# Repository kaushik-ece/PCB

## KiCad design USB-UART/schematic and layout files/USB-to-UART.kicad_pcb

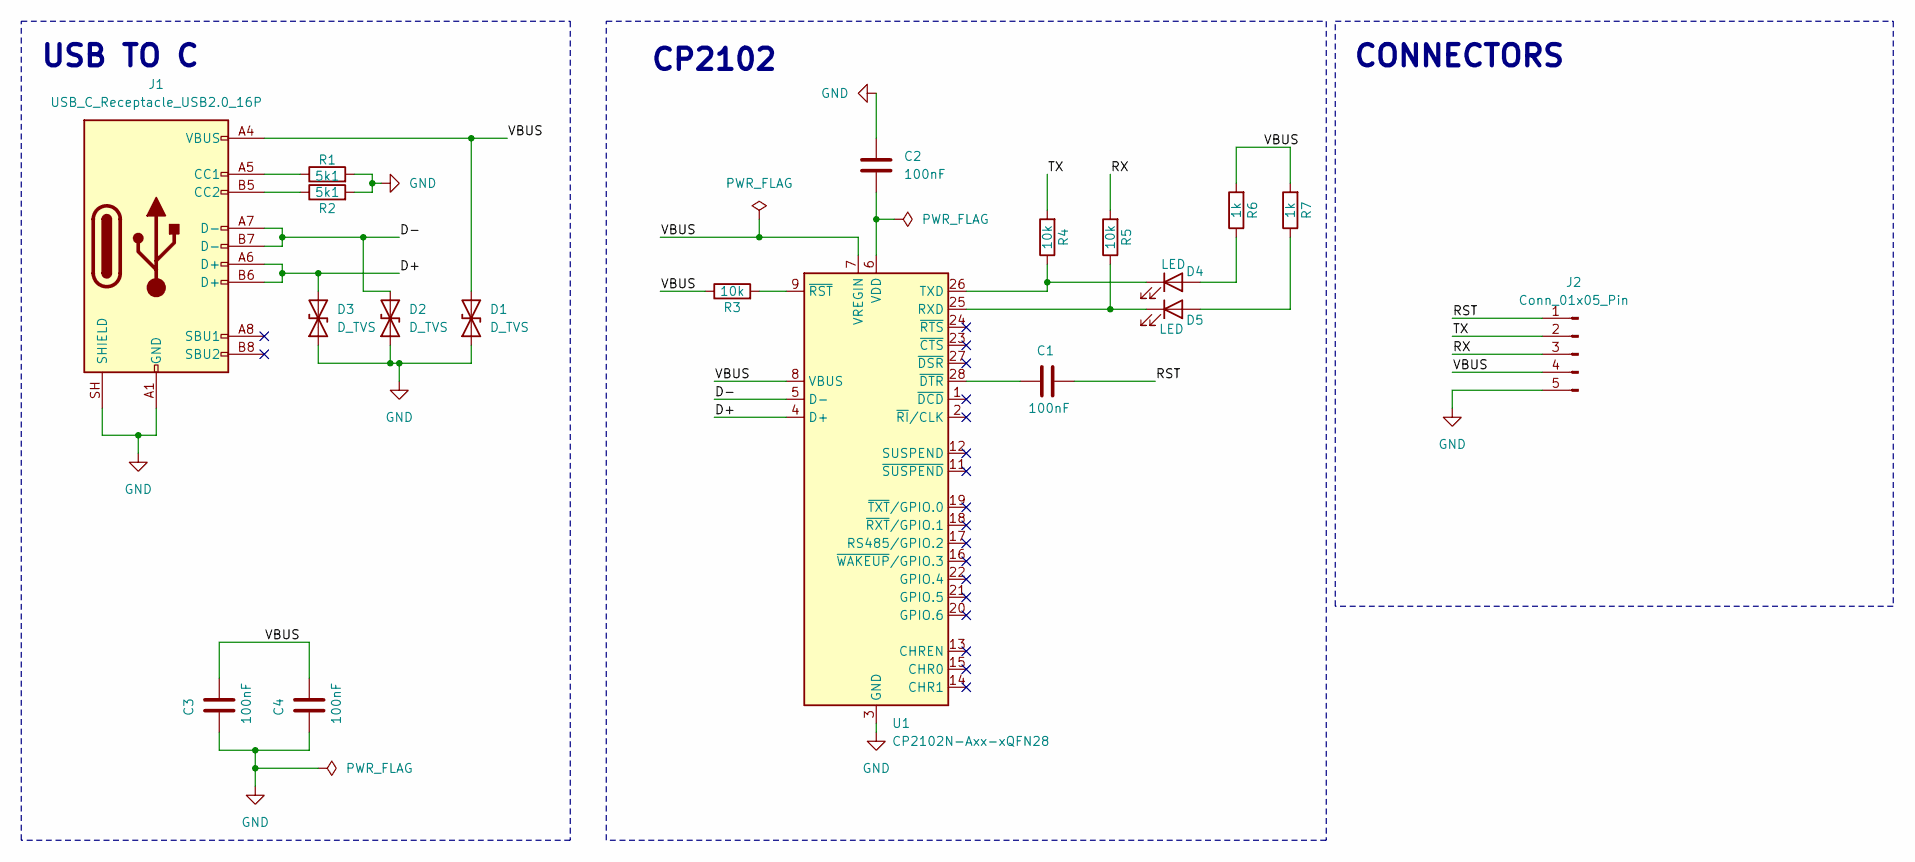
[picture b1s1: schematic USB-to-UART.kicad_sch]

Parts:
C1, C2, C3, C4: 100nF; C_0603_1608Metric
D1, D2, D3: D_TVS; D_SOD-523
D4, D5: LED; LED_0603_1608Metric
J1: USB_C_Receptacle_USB2.0_16P; USB_C_Receptacle_HRO_TYPE-C-31-M-12
J2: Conn_01x05_Pin; PinHeader_1x05_P2.54mm_Vertical
R1, R2: 5k1; R_0603_1608Metric
R3, R4, R5: 10k; R_0603_1608Metric
R6, R7: 1k; R_0603_1608Metric
U1: CP2102N-Axx-xQFN28; QFN-28-1EP_5x5mm_P0.5mm_EP3.35x3.35mm

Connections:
/D+: D3.2 (A2), J1.A6 (D+), J1.B6 (D+), U1.4 (D+)
/D-: D2.2 (A2), J1.A7 (D-), J1.B7 (D-), U1.5 (D-)
/RST: C1.2, J2.1
/RX: J2.3, R5.2
/TX: J2.2, R4.2
/VBUS: C3.2, C4.2, D1.2 (A2), J1.A4 (VBUS), J1.A9 (VBUS), J1.B4 (VBUS), J1.B9 (VBUS), J2.4, R3.1, R6.2, R7.2, U1.7 (VREGIN), U1.8 (VBUS)
GND: C2.2, C3.1, C4.1, D1.1 (A1), D2.1 (A1), D3.1 (A1), J1.A1 (GND), J1.A12 (GND), J1.B1 (GND), J1.B12 (GND), J1.SH (SHIELD), J2.5, R1.2, R2.2, U1.3 (GND), U1.29 (GND)
unnamed: D4.2 (A), R6.1
unnamed: D4.1 (K), R4.1, U1.26 (TXD)
unnamed: D5.2 (A), R7.1
unnamed: D5.1 (K), R5.1, U1.25 (RXD)
unnamed: J1.A5 (CC1), R1.1
unnamed: J1.B5 (CC2), R2.1
unnamed: C2.1, U1.6 (VDD)
unnamed: C1.1, U1.28 (~DTR)
unnamed: R3.2, U1.9 (~RST)

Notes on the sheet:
USB TO C
CP2102
CONNECTORS

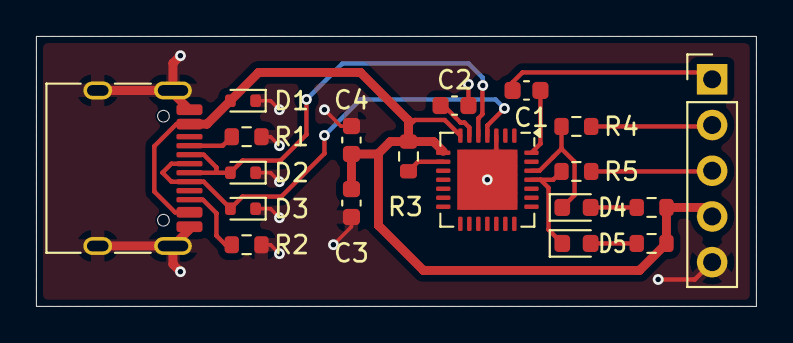
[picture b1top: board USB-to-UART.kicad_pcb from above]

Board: 2 copper layers, 40.0 x 15.0 mm, 19 parts (0 on the bottom side), 16 nets.

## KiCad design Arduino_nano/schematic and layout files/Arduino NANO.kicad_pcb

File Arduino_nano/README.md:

# Arduino Nano (ATmega328P) Board

A custom Arduino Nano-compatible board designed in KiCad. It uses an ATmega328P in a QFN-32 package, an FT232RL for USB-to-serial, and a mini-USB connector. The 5 V rail comes from USB or from the VCC pin through an LM1117-5.0 regulator. All I/O pins are brought out on two 15-pin headers. It is built on a 4-layer PCB.

## What is Arduino Nano?

The Arduino Nano is a small, breadboard-friendly microcontroller board built around the ATmega328P. It is programmed through the Arduino IDE over USB and is widely used for prototypes, robotics, sensor projects and learning embedded systems.

| Feature | ATmega328P |
|---|---|
| Architecture | 8-bit AVR |
| Logic level | 5 V |
| Flash | 32 KB |
| SRAM | 2 KB |
| EEPROM | 1 KB |
| Digital I/O | 14 (D0 to D13) |
| Analog inputs | 8 (A0 to A7), 10-bit ADC |
| Interfaces | UART, SPI, I²C, PWM |

## Features

- ATmega328P-MU microcontroller (QFN-32)
- FT232RL USB-to-UART bridge with auto-reset (RTS through a 100 nF capacitor to RESET)
- Mini-USB (type B) connector
- LM1117-5.0 regulator for the 5 V rail
- Diode (D2) between USB VBUS and the 5 V rail
- 3.3 V output from the FT232RL, available on header pin +3V3
- Resonator (Y2) as the clock source
- RESET button
- User LED (yellow) on D13, TX/RX indicator LEDs on the FT232RL CBUS pins
- Two 3-pin ICSP-style headers (J6, J7) for SPI programming
- Two 1×15 pin headers (J4, J2) for I/O
- Test points TP1, TP2 on the USB data lines
- 4-layer PCB

## PCB Stackup

| Layer | Name | Use |
|:-:|---|---|
| 1 | F.Cu | Signal and components |
| 2 | In1.Cu | GND plane |
| 3 | In2.Cu | Power plane (+3.3 V) |
| 4 | B.Cu | Signal |

## Pinout

### J4 (top header)

| Pin | Name | Pin | Name |
|:-:|:-:|:-:|:-:|
| 1 | D1/TX | 9 | D6 |
| 2 | D0/RX | 10 | D7 |
| 3 | RESET | 11 | D8 |
| 4 | GND | 12 | D9 |
| 5 | D2 | 13 | D10 |
| 6 | D3 | 14 | D11/MOSI |
| 7 | D4 | 15 | D12/MISO |
| 8 | D5 | | |

### J2 (bottom header)

| Pin | Name | Pin | Name |
|:-:|:-:|:-:|:-:|
| 1 | VCC | 9 | A3 |
| 2 | GND | 10 | A2 |
| 3 | RESET | 11 | A1 |
| 4 | +5V | 12 | A0 |
| 5 | A7 | 13 | AREF |
| 6 | A6 | 14 | +3V3 |
| 7 | A5 | 15 | D13/SCK |
| 8 | A4 | | |

### ICSP headers (J6, J7)

| J7 Pin | Name | J6 Pin | Name |
|:-:|:-:|:-:|:-:|
| 1 | D12/MISO | 1 | +5V |
| 2 | D13/SCK | 2 | D11/MOSI |
| 3 | RESET | 3 | GND |

> Logic is 5 V. Do not apply more than 5 V to any I/O pin.

## Schematic

| Block | Purpose |
|---|---|
| MCU | ATmega328P (U1), resonator Y2, RESET button SW1, D13 LED D1, decoupling C1 to C4 |
| USB | Mini-USB J1, FT232RL (U3), TX/RX LEDs, C9 to C12, test points TP1/TP2 |
| Power | LM1117-5.0 (U2), C7, C8, D2 |
| Connection | J4, J2 headers and J6, J7 ICSP headers |

## PCB

### Layout

## Bill of Materials

| Reference | Value | Qty |
|---|---|:-:|
| U1 | ATmega328P-MU | 1 |
| U2 | LM1117LD-5.0 | 1 |
| U3 | FT232RL | 1 |
| Y2 | Resonator | 1 |
| D1 | LED (yellow) | 1 |
| D3 | LED (TX/RX indicators) | 2 |
| D2 | Diode | 1 |
| F1 | Fuse | 1 |
| C3, C10, C11 | 100 nF | 3 |
| C1, C2, C7, C8, C9 | 1 µF | 5 |
| C4, C12 | 4.7 µF, 16 V | 2 |
| R1 to R7 | 1 kΩ | 7 |
| SW1 | Tactile switch | 1 |
| J1 | Mini-USB B connector | 1 |
| J4, J2 | 1×15 pin header, 2.54 mm | 2 |
| J6, J7 | 1×3 pin header, 2.54 mm | 2 |

## Usage

1. Install the FTDI driver if the COM port does not appear.
2. Connect the board to your PC with a mini-USB cable.
3. In Arduino IDE, select **Arduino Nano** and the **ATmega328P** processor.
4. Select the COM port and upload.

A new ATmega328P has no bootloader. Burn it once through the ICSP headers (J6, J7) with an ISP programmer, using **Tools > Burn Bootloader**.

Test sketch (blinks the yellow LED on D13):

```cpp
void setup() {
  pinMode(13, OUTPUT);
}

void loop() {
  digitalWrite(13, HIGH);
  delay(500);
  digitalWrite(13, LOW);
  delay(500);
}
```

## Files

| File | Description |
|---|---|
| `ARDUINO_schematic.png` | Schematic image |
| `ARDUINO_layout.png` | PCB layout image |
| `ARDUINO_3D.png` | 3D render |
| `ATMEGA328P-MU.STEP` | 3D model of the ATmega328P |
| `LM1117LD-5_0_NOPB.STEP` | 3D model of the LM1117-5.0 |

Open the KiCad project in KiCad 10 or newer.

## Author

Kaushik, B.E. Electronics and Communication Engineering, Chennai Institute of Technology

## License

MIT License

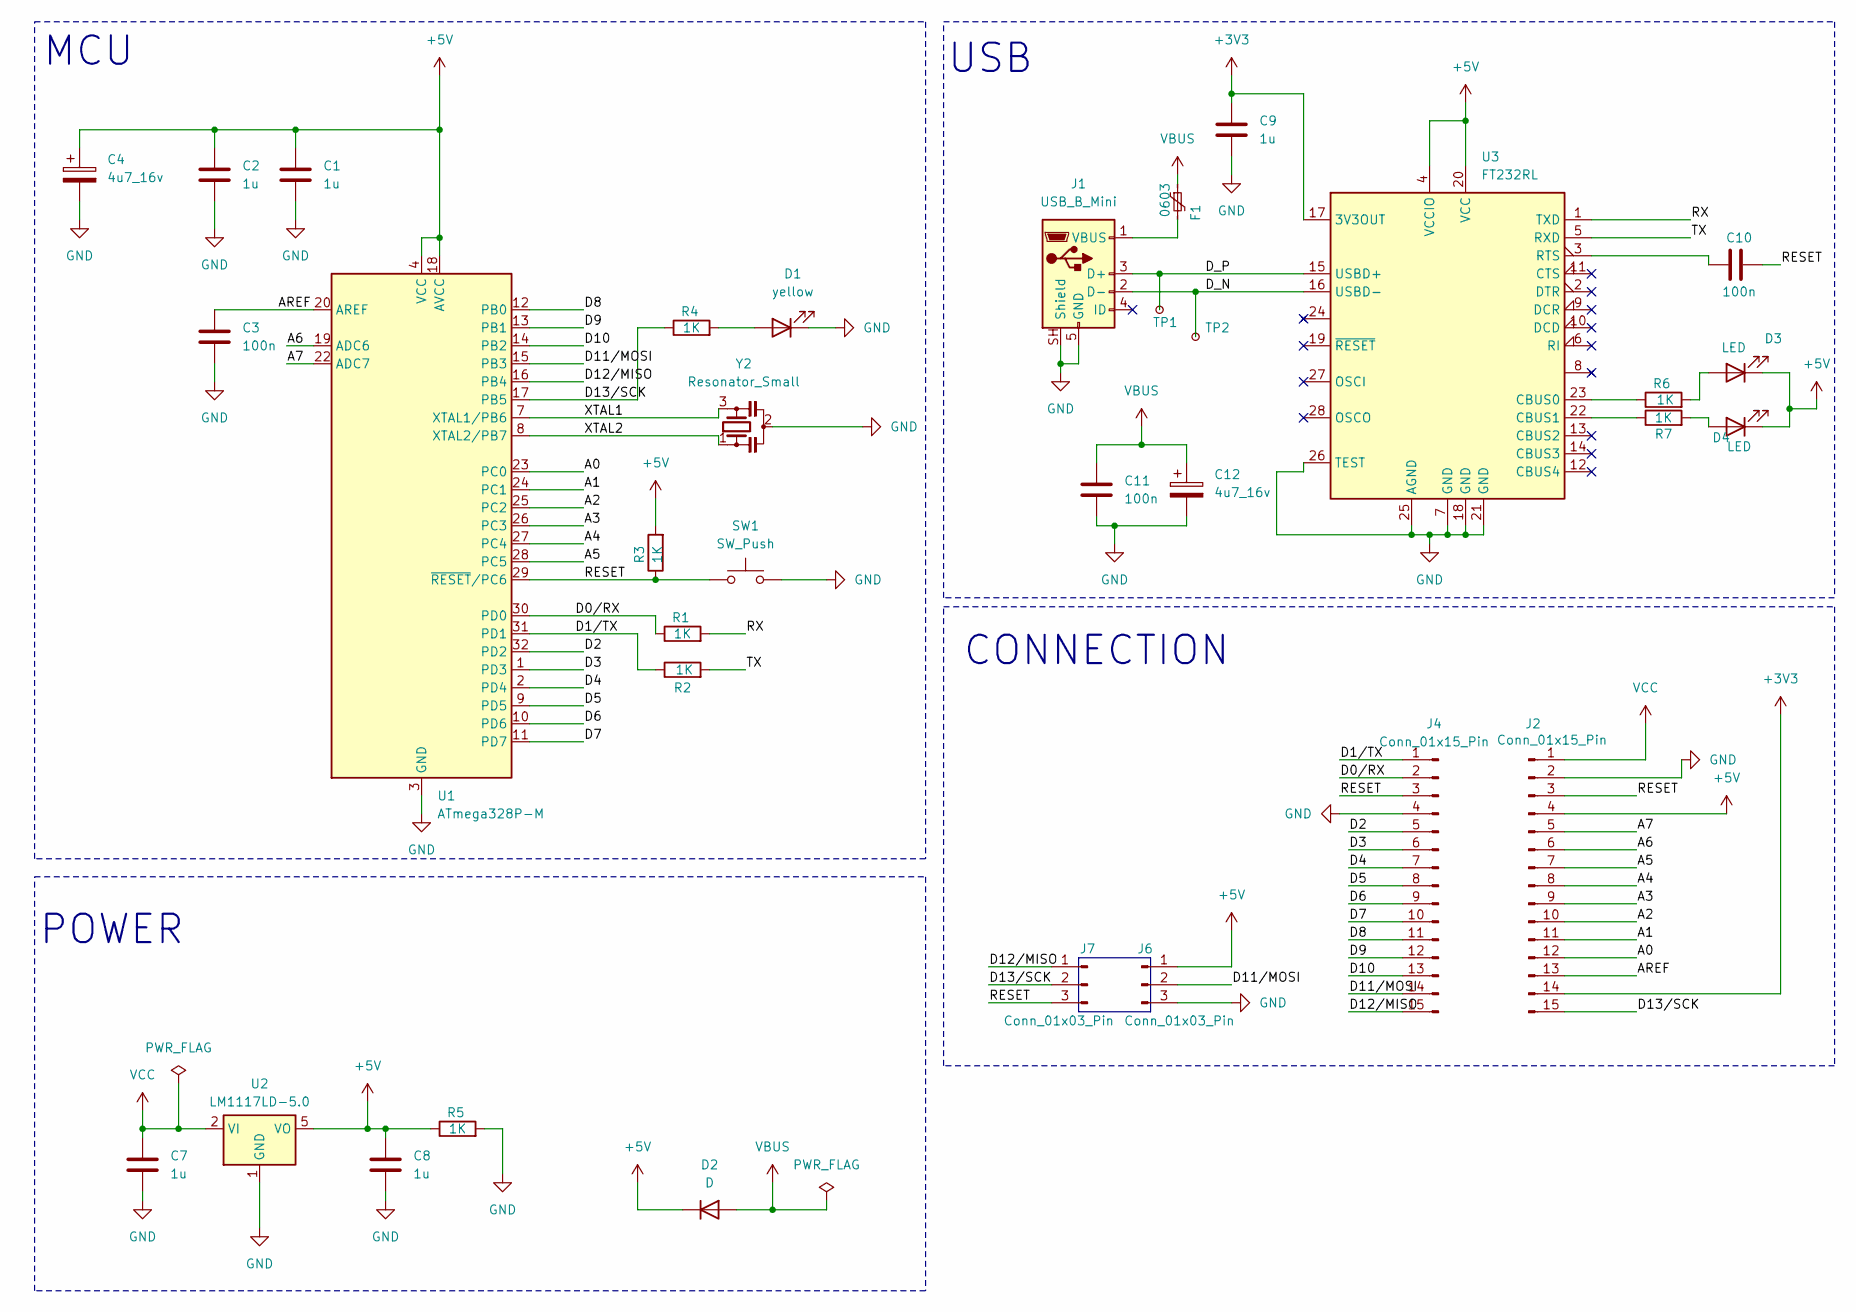
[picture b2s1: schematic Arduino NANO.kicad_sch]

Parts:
C1, C2, C7, C8, C9: 1u; C_0603_1608Metric
C3, C10, C11: 100n; C_0603_1608Metric
C4, C12: 4u7_16v; CP_EIA-3216-10_Kemet-I_HandSolder
D1: yellow; LED_0805_2012Metric
D2: D; D_0805_2012Metric
D3, D4: LED; LED_0805_2012Metric
F1: 0603; Fuse_0603_1608Metric
J1: USB_B_Mini; USB_Mini-B_Lumberg_2486_01_Horizontal
J2, J4: Conn_01x15_Pin; PinHeader_1x15_P2.54mm_Vertical
J6, J7: Conn_01x03_Pin; PinHeader_1x03_P2.54mm_Vertical
R1, R2, R3, R4, R5, R6, R7: 1K; R_0603_1608Metric
SW1: SW_Push; SW_Push_SPST_NO_Alps_SKRK
TP1, TP2: TestPoint_Small; TestPoint_Pad_D1.0mm
U1: ATmega328P-M; QFN-32-1EP_5x5mm_P0.5mm_EP3.1x3.1mm
U2: LM1117LD-5.0; WSON-8-1EP_4x4mm_P0.8mm_EP2.2x3mm
U3: FT232RL; SSOP-28_5.3x10.2mm_P0.65mm
Y2: Resonator_Small; Resonator_SMD_Murata_CSTxExxV-3Pin_3.0x1.1mm

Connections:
+3V3: C9.1, J2.14, U3.17 (3V3OUT)
+5V: C1.1, C2.1, C4.1, C8.1, D2.1 (K), D3.1 (K), D4.1 (K), J2.4, J6.1, R3.2, R5.1, U1.4 (VCC), U1.6 (VCC), U1.18 (AVCC), U2.5 (VO), U2.6 (VO), U2.7 (VO), U2.9 (VO), U3.4 (VCCIO), U3.20 (VCC)
/A0: J2.12, U1.23 (PC0)
/A1: J2.11, U1.24 (PC1)
/A2: J2.10, U1.25 (PC2)
/A3: J2.9, U1.26 (PC3)
/A4: J2.8, U1.27 (PC4)
/A5: J2.7, U1.28 (PC5)
/A6: J2.6, U1.19 (ADC6)
/A7: J2.5, U1.22 (ADC7)
/AREF: C3.1, J2.13, U1.20 (AREF)
/D0/RX: J4.2, R1.1, U1.30 (PD0)
/D1/TX: J4.1, R2.1, U1.31 (PD1)
/D2: J4.5, U1.32 (PD2)
/D3: J4.6, U1.1 (PD3)
/D4: J4.7, U1.2 (PD4)
/D5: J4.8, U1.9 (PD5)
/D6: J4.9, U1.10 (PD6)
/D7: J4.10, U1.11 (PD7)
/D8: J4.11, U1.12 (PB0)
/D9: J4.12, U1.13 (PB1)
/D10: J4.13, U1.14 (PB2)
/D11/MOSI: J4.14, J6.2, U1.15 (PB3)
/D12/MISO: J4.15, J7.1, U1.16 (PB4)
/D13/SCK: J2.15, J7.2, R4.1, U1.17 (PB5)
/D_N: J1.2 (D-), TP2.1 (1_1), U3.16 (USBD-)
/D_P: J1.3 (D+), TP1.1 (1_1), U3.15 (USBD+)
/RESET: C10.2, J2.3, J4.3, J7.3, R3.1, SW1.1, U1.29 (~RESET/PC6)
/RX: R1.2, U3.1 (TXD)
/TX: R2.2, U3.5 (RXD)
/XTAL1: U1.7 (XTAL1/PB6), Y2.3
/XTAL2: U1.8 (XTAL2/PB7), Y2.1
GND: C1.2, C2.2, C3.2, C4.2, C7.2, C8.2, C9.2, C11.2, C12.2, D1.1 (K), J1.5 (GND), J1.SH (Shield), J2.2, J4.4, J6.3, R5.2, SW1.2, U1.3 (GND), U1.5 (GND), U1.21 (GND), U1.33 (GND), U2.1 (GND), U3.7 (GND), U3.18 (GND), U3.21 (GND), U3.25 (AGND), U3.26 (TEST), Y2.2
unnamed: D1.2 (A), R4.2
unnamed: D3.2 (A), R6.2
unnamed: D4.2 (A), R7.2
unnamed: F1.2, J1.1 (VBUS)
unnamed: R6.1, U3.23 (CBUS0)
unnamed: R7.1, U3.22 (CBUS1)
unnamed: C10.1, U3.3 (RTS)
VBUS: C11.1, C12.1, D2.2 (A), F1.1
VCC: C7.1, J2.1, U2.2 (VI), U2.3 (VI), U2.4 (VI)

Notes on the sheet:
USB
MCU
CONNECTION
POWER

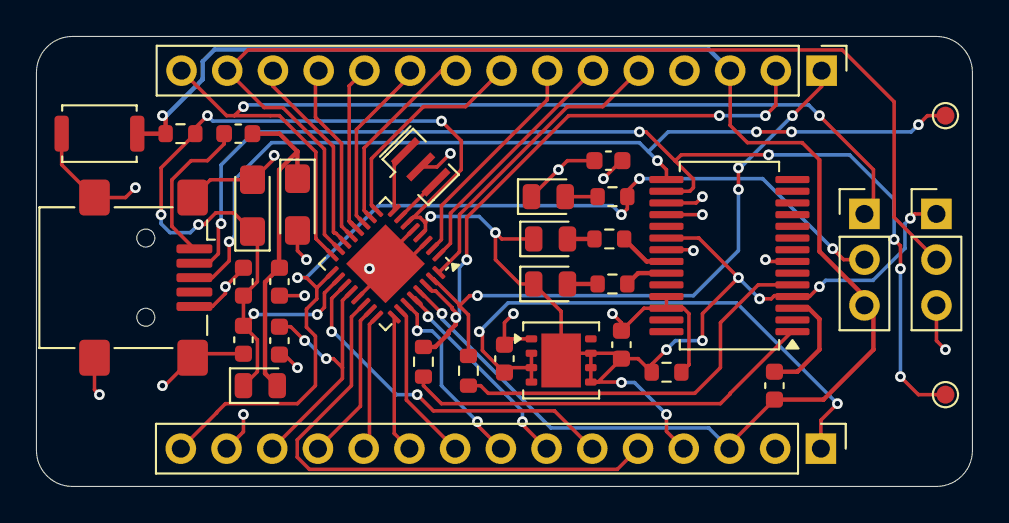
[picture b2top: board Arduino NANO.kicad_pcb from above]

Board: 4 copper layers, 52.0 x 25.0 mm, 34 parts (0 on the bottom side), 42 nets.

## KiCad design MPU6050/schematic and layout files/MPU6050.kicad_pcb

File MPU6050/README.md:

# MPU-6050 Breakout Board

A small breakout board for the MPU-6050 (3-axis gyroscope + 3-axis accelerometer), designed in KiCad. It runs from a 5 V supply, regulates it to 3.3 V on board, and brings out the I²C pins on an 8-pin header.

## Features

- MPU-6050 6-axis motion sensor, I²C interface
- On-board 3.3 V regulator (AP2112K-3.3), powered from 5 V
- On-board I²C pull-up resistors (2.2 kΩ)
- Selectable I²C address: `0x68` (default) or `0x69`
- 2-layer board, 25.8 mm × 22.3 mm, two 2.5 mm mounting holes

## Pinout

| Pin | Name | Description |
|:-:|:-:|---|
| 1 | VCC | 5 V input |
| 2 | GND | Ground |
| 3 | SCL | I²C clock |
| 4 | SDA | I²C data |
| 5 | XDA | Auxiliary I²C data |
| 6 | XCL | Auxiliary I²C clock |
| 7 | AD0 | Address select (low = `0x68`, high = `0x69`) |
| 8 | INT | Interrupt output |

> The I²C lines are pulled up to 3.3 V. Use a 3.3 V microcontroller (for example ESP32) or add a level shifter for 5 V logic.

## Schematic

## PCB

### Layout

### Back view

## Bill of Materials

| Reference | Value | Package | Qty |
|---|---|---|:-:|
| U1 | AP2112K-3.3 | SOT-23-5 | 1 |
| U2 | MPU-6050 | QFN-24 (4×4 mm) | 1 |
| C1, C3, C4 | 100 nF | 0603 | 3 |
| C2, C7 | 10 µF | 0805 | 2 |
| C5 | 2.2 nF | 0805 | 1 |
| R1 | 100 kΩ | 0603 | 1 |
| R2 | 1 kΩ | 0603 | 1 |
| R3, R4 | 2.2 kΩ | 0603 | 2 |
| R5 | 4.7 kΩ | 0603 | 1 |
| J1 | 1×8 pin header, 2.54 mm | Through-hole | 1 |

## Usage

Connect the board to an ESP32:

| Board | ESP32 |
|---|---|
| VCC | 5 V |
| GND | GND |
| SDA | GPIO 21 |
| SCL | GPIO 22 |

Test sketch (reads the WHO_AM_I register, which should return `0x68`):

```cpp
#include <Wire.h>

void setup() {
  Serial.begin(115200);
  Wire.begin();

  Wire.beginTransmission(0x68);
  Wire.write(0x6B);            // wake the sensor
  Wire.write(0x00);
  Wire.endTransmission();

  Wire.beginTransmission(0x68);
  Wire.write(0x75);            // WHO_AM_I register
  Wire.endTransmission(false);
  Wire.requestFrom(0x68, 1);
  Serial.println(Wire.read(), HEX);
}

void loop() {}
```

## Files

| File | Description |
|---|---|
| `MPU6050.zip` | KiCad project (schematic and PCB) and Gerber files |
| `schematic.png` | Schematic image |
| `pcb-layout.png` | PCB layout image |
| `pcb-3d-top.png`, `pcb-3d-bottom.png` | 3D renders |

Extract `MPU6050.zip` and open `MPU6050.kicad_pro` in KiCad 10 or newer. The Gerber files can be uploaded directly to a PCB manufacturer.

## Known issue (Rev 1.0)

The EN pin (pin 3) of the AP2112K regulator is not connected. It should be tied to VIN (pin 1). On a built board, solder a short wire between these two pins. This will be fixed in the next revision.

## Author

Kaushik, B.E. Electronics and Communication Engineering, Chennai Institute of Technology

## License

MIT License

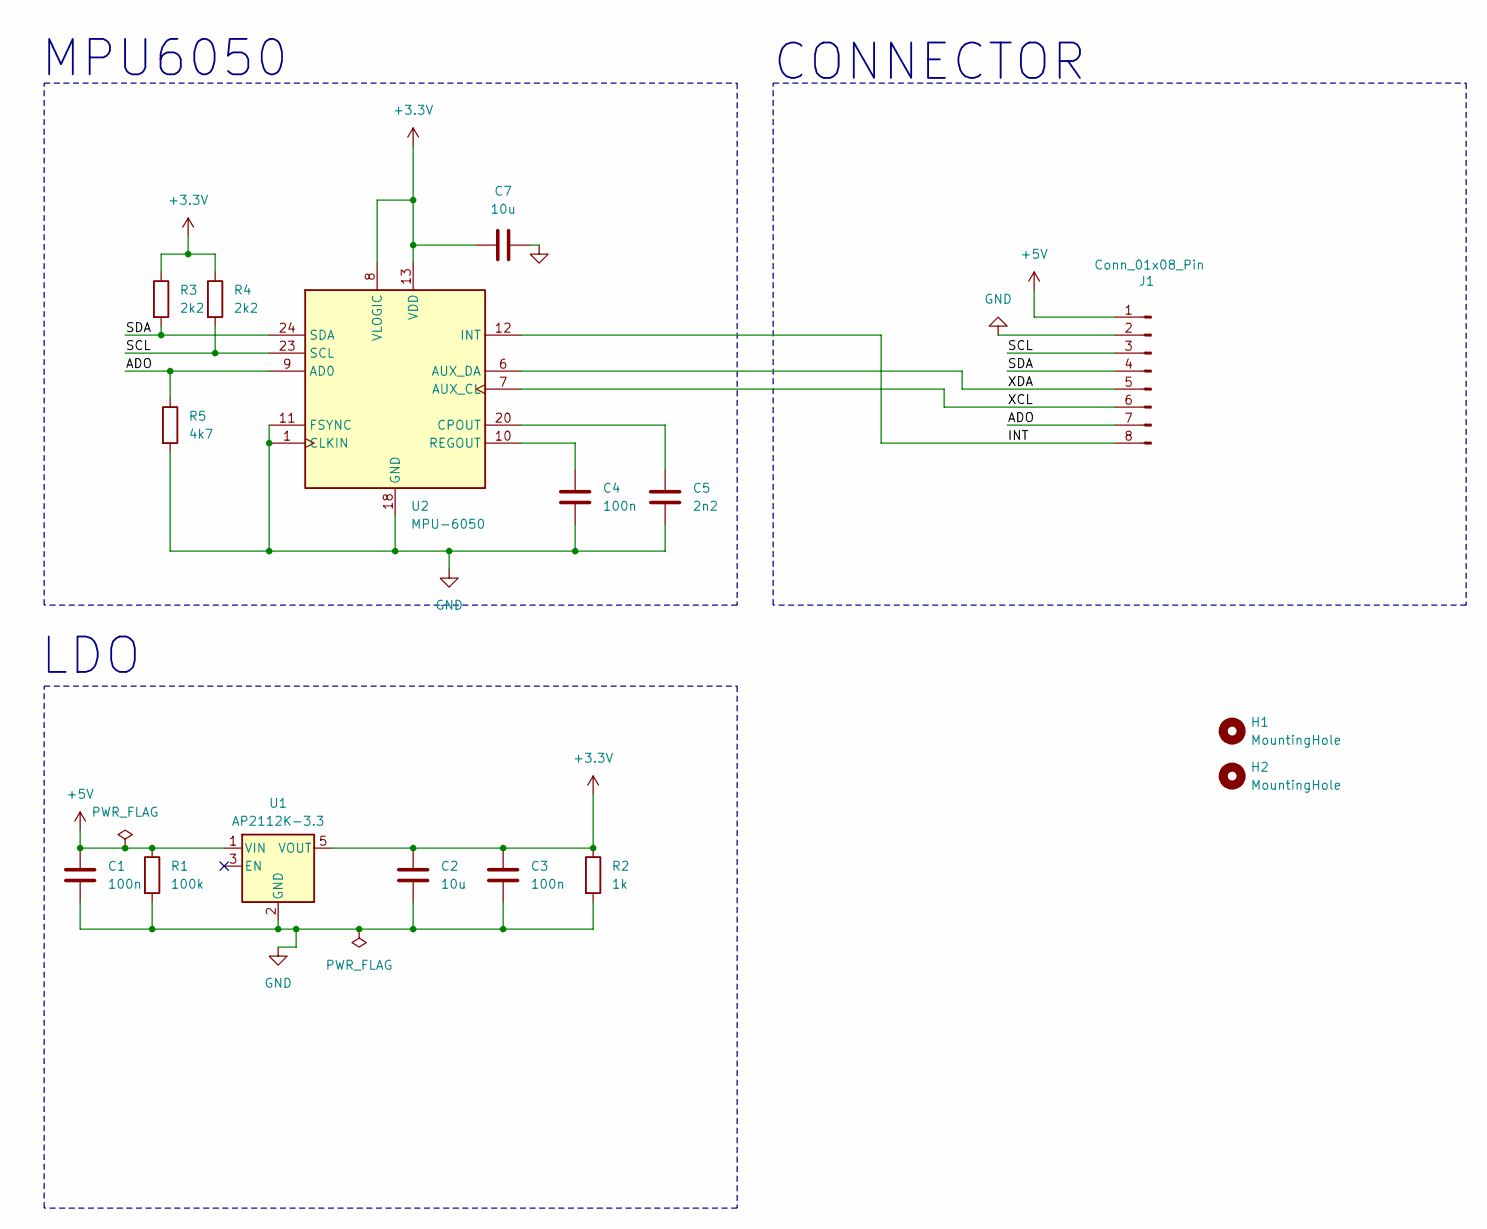
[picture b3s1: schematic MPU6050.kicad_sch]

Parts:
C1, C3, C4: 100n; C_0603_1608Metric
C2, C7: 10u; C_0805_2012Metric
C5: 2n2; C_0805_2012Metric
H1, H2: MountingHole; MountingHole_2.5mm
J1: Conn_01x08_Pin; PinHeader_1x08_P2.54mm_Vertical
R1: 100k; R_0603_1608Metric
R2: 1k; R_0603_1608Metric
R3, R4: 2k2; R_0603_1608Metric
R5: 4k7; R_0603_1608Metric
U1: AP2112K-3.3; SOT-23-5
U2: MPU-6050; InvenSense_QFN-24_4x4mm_P0.5mm

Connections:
+3.3V: C2.1, C3.1, C7.1, R2.1, R3.1, R4.1, U1.5 (VOUT), U2.8 (VLOGIC), U2.13 (VDD)
+5V: C1.1, J1.1, R1.1, U1.1 (VIN)
/ADO: J1.7, R5.1, U2.9 (AD0)
/INT: J1.8, U2.12 (INT)
/SCL: J1.3, R4.2, U2.23 (SCL)
/SDA: J1.4, R3.2, U2.24 (SDA)
/XCL: J1.6, U2.7 (AUX_CL)
/XDA: J1.5, U2.6 (AUX_DA)
GND: C1.2, C2.2, C3.2, C4.2, C5.2, C7.2, J1.2, R1.2, R2.2, R5.2, U1.2 (GND), U2.1 (CLKIN), U2.11 (FSYNC), U2.18 (GND)
unnamed: C5.1, U2.20 (CPOUT)
unnamed: C4.1, U2.10 (REGOUT)

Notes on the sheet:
CONNECTOR
MPU6050
LDO

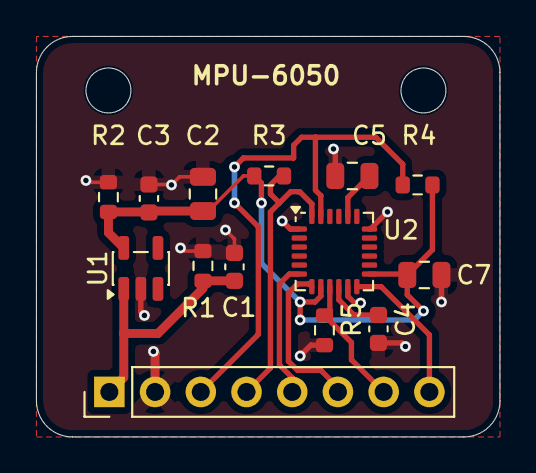
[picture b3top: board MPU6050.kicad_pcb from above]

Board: 2 copper layers, 25.8 x 22.2 mm, 16 parts (0 on the bottom side), 11 nets.

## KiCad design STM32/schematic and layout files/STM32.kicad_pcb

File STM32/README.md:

# STM32F103C8T6 Development Board

A simple STM32 development board built around the **STM32F103C8T6** (Arm Cortex-M3, LQFP-48), designed in KiCad. It is powered over USB, has an on-board 3.3 V regulator, and brings out SWD, USART and I²C on separate headers.

## Features

- STM32F103C8T6 microcontroller (Cortex-M3, 72 MHz)
- Micro-USB connector for power and USB data (PA11 / PA12)
- 3.3 V regulator (AMS1117-3.3) with a red power LED
- 16 MHz crystal (HSE)
- SWD header for programming and debugging
- USART header and I²C header
- BOOT switch to select the BOOT0 level
- Filtered analog supply (ferrite bead on VDDA)
- Four mounting holes

## Main Components

| Part | Function |
|---|---|
| STM32F103C8T6 (U1) | Microcontroller |
| AMS1117-3.3 (U2) | 5 V to 3.3 V regulator |
| 16 MHz crystal (Y1) | External clock |
| Micro-USB (J1) | Power and USB data |
| Ferrite bead (FB1) | VDDA supply filter |
| Red LED (D1) | Power indicator |
| SPDT switch (SW1) | BOOT0 selection |

## Headers

All headers are 1×4, 2.54 mm pitch.

| Pin | USART (J3) | SWD (J2) | I²C (J4) |
|:-:|---|---|---|
| 1 | 3.3 V | 3.3 V | 3.3 V |
| 2 | USART1_TX | SWDIO | I2C2_SCL |
| 3 | USART1_RX | SWCLK | I2C2_SDA |
| 4 | GND | GND | GND |

## Pin Usage

| Function | MCU pin |
|---|---|
| USB D− / D+ | PA11 / PA12 |
| SWDIO / SWCLK | PA13 / PA14 |
| USART1 TX / RX | PB6 / PB7 |
| I2C2 SCL / SDA | PB10 / PB11 |
| HSE crystal | PD0 / PD1 |

The I²C lines have pull-up resistors to 3.3 V on the board.

## Schematic

## PCB Layout

## Getting Started

1. Connect the board to a PC with a micro-USB cable. The red LED turns on when the 3.3 V rail is up.
2. Connect an ST-Link to the SWD header: 3.3 V, SWDIO, SWCLK and GND.
3. Open your project in STM32CubeIDE (or any STM32 toolchain), select the `STM32F103C8Tx` device and flash it.

## Files

| File | Description |
|---|---|
| `STM32_sch.png` | Schematic image |
| `STM32_Layout.png` | PCB layout image |
| `STM32_3D.png` | 3D render |

KiCad project files and Gerbers are in the project zip. Open the `.kicad_pro` file in KiCad 10 or newer.

## Author

Kaushik, B.E. Electronics and Communication Engineering, Chennai Institute of Technology

## License

MIT License

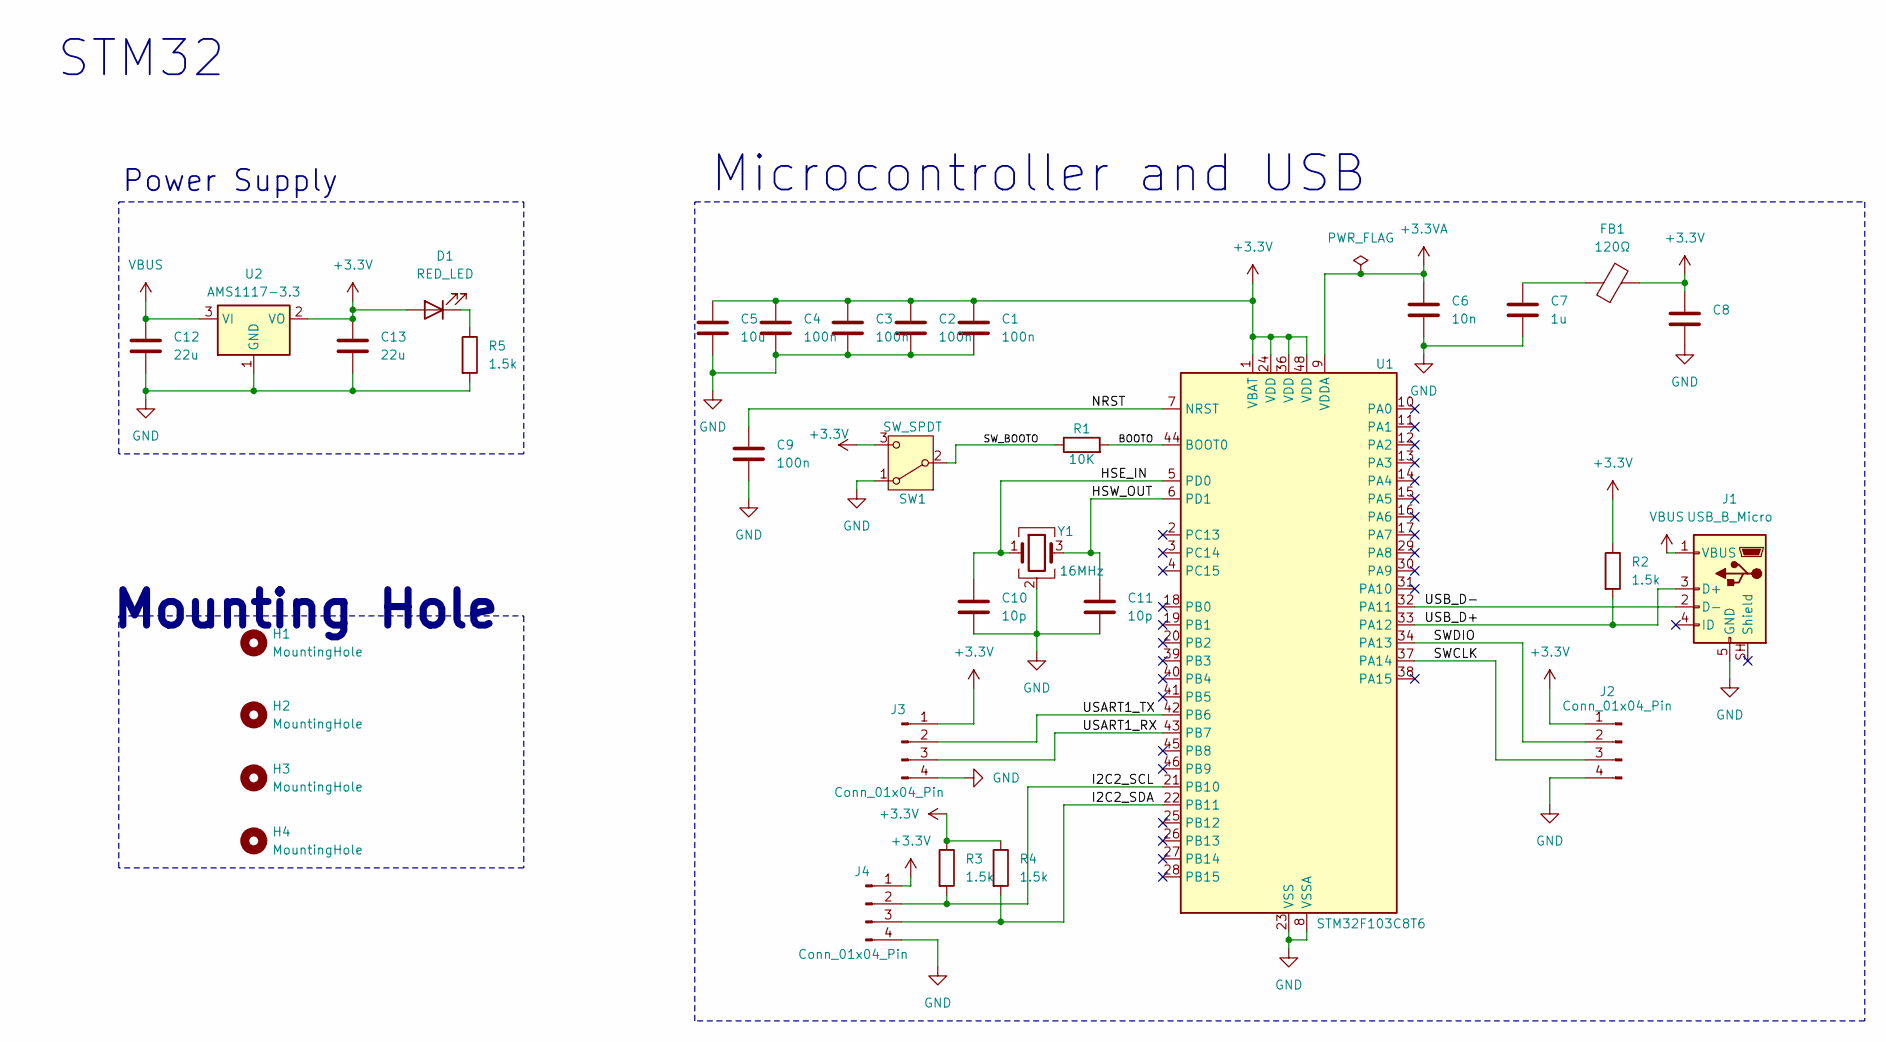
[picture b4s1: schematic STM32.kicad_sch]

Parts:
C1, C2, C3, C4, C9: 100n; C_0402_1005Metric
C5: 10u; C_0603_1608Metric
C6: 10n; C_0402_1005Metric
C7, C8: 1u; C_0402_1005Metric
C10, C11: 10p; C_0402_1005Metric
C12, C13: 22u; C_0805_2012Metric
D1: RED_LED; LED_0603_1608Metric
FB1: 120Ω; L_0603_1608Metric
H1, H2, H3, H4: MountingHole; MountingHole_2.1mm
J1: USB_B_Micro; USB_Micro-B_Wuerth_629105150521
J2, J3, J4: Conn_01x04_Pin; PinHeader_1x04_P2.54mm_Vertical
R1: 10K; R_0402_1005Metric
R2, R3, R4, R5: 1.5k; R_0402_1005Metric
SW1: SW_SPDT; SW_SPDT_PCM12
U1: STM32F103C8T6; LQFP-48_7x7mm_P0.5mm
U2: AMS1117-3.3; SOT-223-3_TabPin2
Y1: 16MHz; Crystal_SMD_3225-4Pin_3.2x2.5mm

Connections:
+3.3V: C1.1, C2.1, C3.1, C4.1, C5.1, C8.1, C13.1, D1.2 (A), FB1.2, J2.1, J3.1, J4.1, R2.1, R3.1, R4.1, SW1.3 (C), U1.1 (VBAT), U1.24 (VDD), U1.36 (VDD), U1.48 (VDD), U2.2 (VO)
+3.3VA: C6.1, U1.9 (VDDA)
/BOOTO: R1.2, U1.44 (BOOT0)
/HSE_IN: C10.1, U1.5 (PD0), Y1.1
/HSW_OUT: C11.1, U1.6 (PD1), Y1.3
/I2C2_SCL: J4.2, R3.2, U1.21 (PB10)
/I2C2_SDA: J4.3, R4.2, U1.22 (PB11)
/NRST: C9.1, U1.7 (NRST)
/SWCLK: J2.3, U1.37 (PA14)
/SWDIO: J2.2, U1.34 (PA13)
/SW_BOOTO: R1.1, SW1.2 (B)
/USART1_RX: J3.3, U1.43 (PB7)
/USART1_TX: J3.2, U1.42 (PB6)
/USB_D+: J1.3 (D+), R2.2, U1.33 (PA12)
/USB_D-: J1.2 (D-), U1.32 (PA11)
GND: C1.2, C2.2, C3.2, C4.2, C5.2, C6.2, C7.2, C8.2, C9.2, C10.2, C11.2, C12.2, C13.2, J1.5 (GND), J2.4, J3.4, J4.4, R5.2, SW1.1 (A), U1.8 (VSSA), U1.23 (VSS), U1.35 (VSS), U1.47 (VSS), U2.1 (GND), Y1.2 (G), Y1.4 (G)
unnamed: C7.1, FB1.1
unnamed: D1.1 (K), R5.1
VBUS: C12.1, J1.1 (VBUS), U2.3 (VI)

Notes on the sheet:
STM32
Power Supply
Microcontroller and USB
Mounting Hole

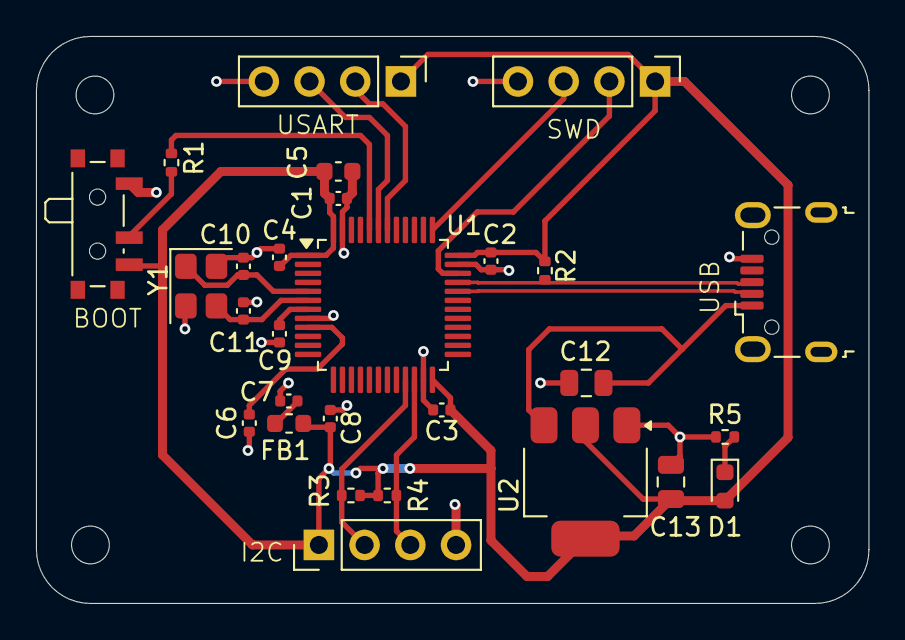
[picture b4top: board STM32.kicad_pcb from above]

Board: 2 copper layers, 46.2 x 31.5 mm, 32 parts (0 on the bottom side), 19 nets.

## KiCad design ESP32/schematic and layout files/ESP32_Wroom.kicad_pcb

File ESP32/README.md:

# ESP32-WROOM-32 Development Board

A custom ESP32 development board designed in KiCad. It is powered and programmed over USB-C, regulates 5 V to 3.3 V on board, and brings out the GPIO pins on two 15-pin headers.

## What is ESP32?

The ESP32 is a low-cost, low-power System-on-Chip from Espressif Systems. It combines a dual-core microcontroller with Wi-Fi and Bluetooth, which makes it popular for IoT, wearables, sensors and automation. The ESP32-WROOM-32 is a ready-made module with the chip, flash memory, crystal and PCB antenna in one package.

| Feature | ESP32 |
|---|---|
| CPU | Dual-core Xtensa LX6, up to 240 MHz |
| Wireless | Wi-Fi 802.11 b/g/n, Bluetooth v4.2 (Classic + BLE) |
| Logic level | 3.3 V |
| SRAM | 520 KB |
| Interfaces | UART, SPI, I²C, I²S, PWM, CAN, ADC, DAC, touch |

## Features

- ESP32-WROOM-32 module (Wi-Fi + Bluetooth)
- USB-C input for power and programming
- CH340C USB-to-UART bridge with auto-reset (DTR/RTS through two SS8050 transistors)
- On-board 3.3 V regulator (AMS1117-3.3), powered from 5 V
- RESET (EN) and BOOT (IO0) buttons
- User LED on IO2, red power LED
- Schottky diode (B5819W) on the USB 5 V line
- Two 1×15 pin headers (J2, J3) for GPIO breakout
- Antenna keep-out zone, four mounting holes

## Pinout

### J2

| Pin | Name | Pin | Name |
|:-:|:-:|:-:|:-:|
| 1 | GND | 9 | IO33 |
| 2 | +5V | 10 | IO32 |
| 3 | IO13 | 11 | IO35 |
| 4 | IO12 | 12 | IO34 |
| 5 | IO14 | 13 | VN |
| 6 | IO27 | 14 | VP |
| 7 | IO26 | 15 | EN |
| 8 | IO25 | | |

### J3

| Pin | Name | Pin | Name |
|:-:|:-:|:-:|:-:|
| 1 | GND | 9 | IO18 |
| 2 | +3.3V | 10 | IO19 |
| 3 | IO15 | 11 | IO21 |
| 4 | IO2 | 12 | RXD0 |
| 5 | IO4 | 13 | TXD0 |
| 6 | RXD2 | 14 | IO22 |
| 7 | TXD2 | 15 | IO23 |
| 8 | IO5 | | |

> IO34, IO35, VP and VN are input-only pins. IO0, IO2 and IO15 are strapping pins.

## Schematic

| Block | Purpose |
|---|---|
| Debug Port | USB-C input, CC pull-downs (R4, R5), Schottky diode D1, power LED D4 |
| LDO | AMS1117-3.3 (U2) with C1, C2, C3 |
| LED | User LED D3 on IO2 through R7 |
| USB-UART | CH340C (U3), Q1 and Q2 drive EN and IO0 for auto-reset |
| Microcontroller | ESP32-WROOM-32 (U1), EN pull-up R1, RESET (SW1), BOOT (SW2) |
| Connector | J2 and J3 pin headers |

## PCB

### Layout

The hatched area on the right is the antenna keep-out zone. No copper, components or ground fill are placed there.

## Bill of Materials

| Reference | Value | Qty |
|---|---|:-:|
| U1 | ESP32-WROOM-32 | 1 |
| U2 | AMS1117-3.3 | 1 |
| U3 | CH340C | 1 |
| Q1, Q2 | SS8050 | 2 |
| D1 | B5819W | 1 |
| D3 | LED | 1 |
| D4 | LED (red) | 1 |
| C1, C3, C4, C5, C6 | 100 nF | 5 |
| C2 | 10 µF | 1 |
| R1 | 10 kΩ | 1 |
| R3 | 1 kΩ | 1 |
| R4, R5 | 5.1 kΩ | 2 |
| R7 | 220 Ω | 1 |
| SW1, SW2 | Tactile switch | 2 |
| J1 | USB-C receptacle | 1 |
| J2, J3 | 1×15 pin header, 2.54 mm | 2 |

## Usage

1. Connect the board to your PC with a USB-C cable.
2. Install the CH340 driver if the COM port does not appear.
3. In Arduino IDE, install the ESP32 board package and select **ESP32 Dev Module**.
4. Select the COM port and upload. The auto-reset circuit enters download mode for you.

If the upload cannot connect, hold BOOT, press RESET, then release BOOT.

Test sketch (blinks the on-board LED on IO2):

```cpp
#define LED_PIN 2

void setup() {
  pinMode(LED_PIN, OUTPUT);
}

void loop() {
  digitalWrite(LED_PIN, HIGH);
  delay(500);
  digitalWrite(LED_PIN, LOW);
  delay(500);
}
```

## Files

| File | Description |
|---|---|
| `ESP32_sch.png` | Schematic image |
| `ESP32_layout.png` | PCB layout image |
| `ESP32_3D.png` | 3D render |

Open the KiCad project in KiCad 10 or newer.

## Author

Kaushik, B.E. Electronics and Communication Engineering, Chennai Institute of Technology

## License

MIT License

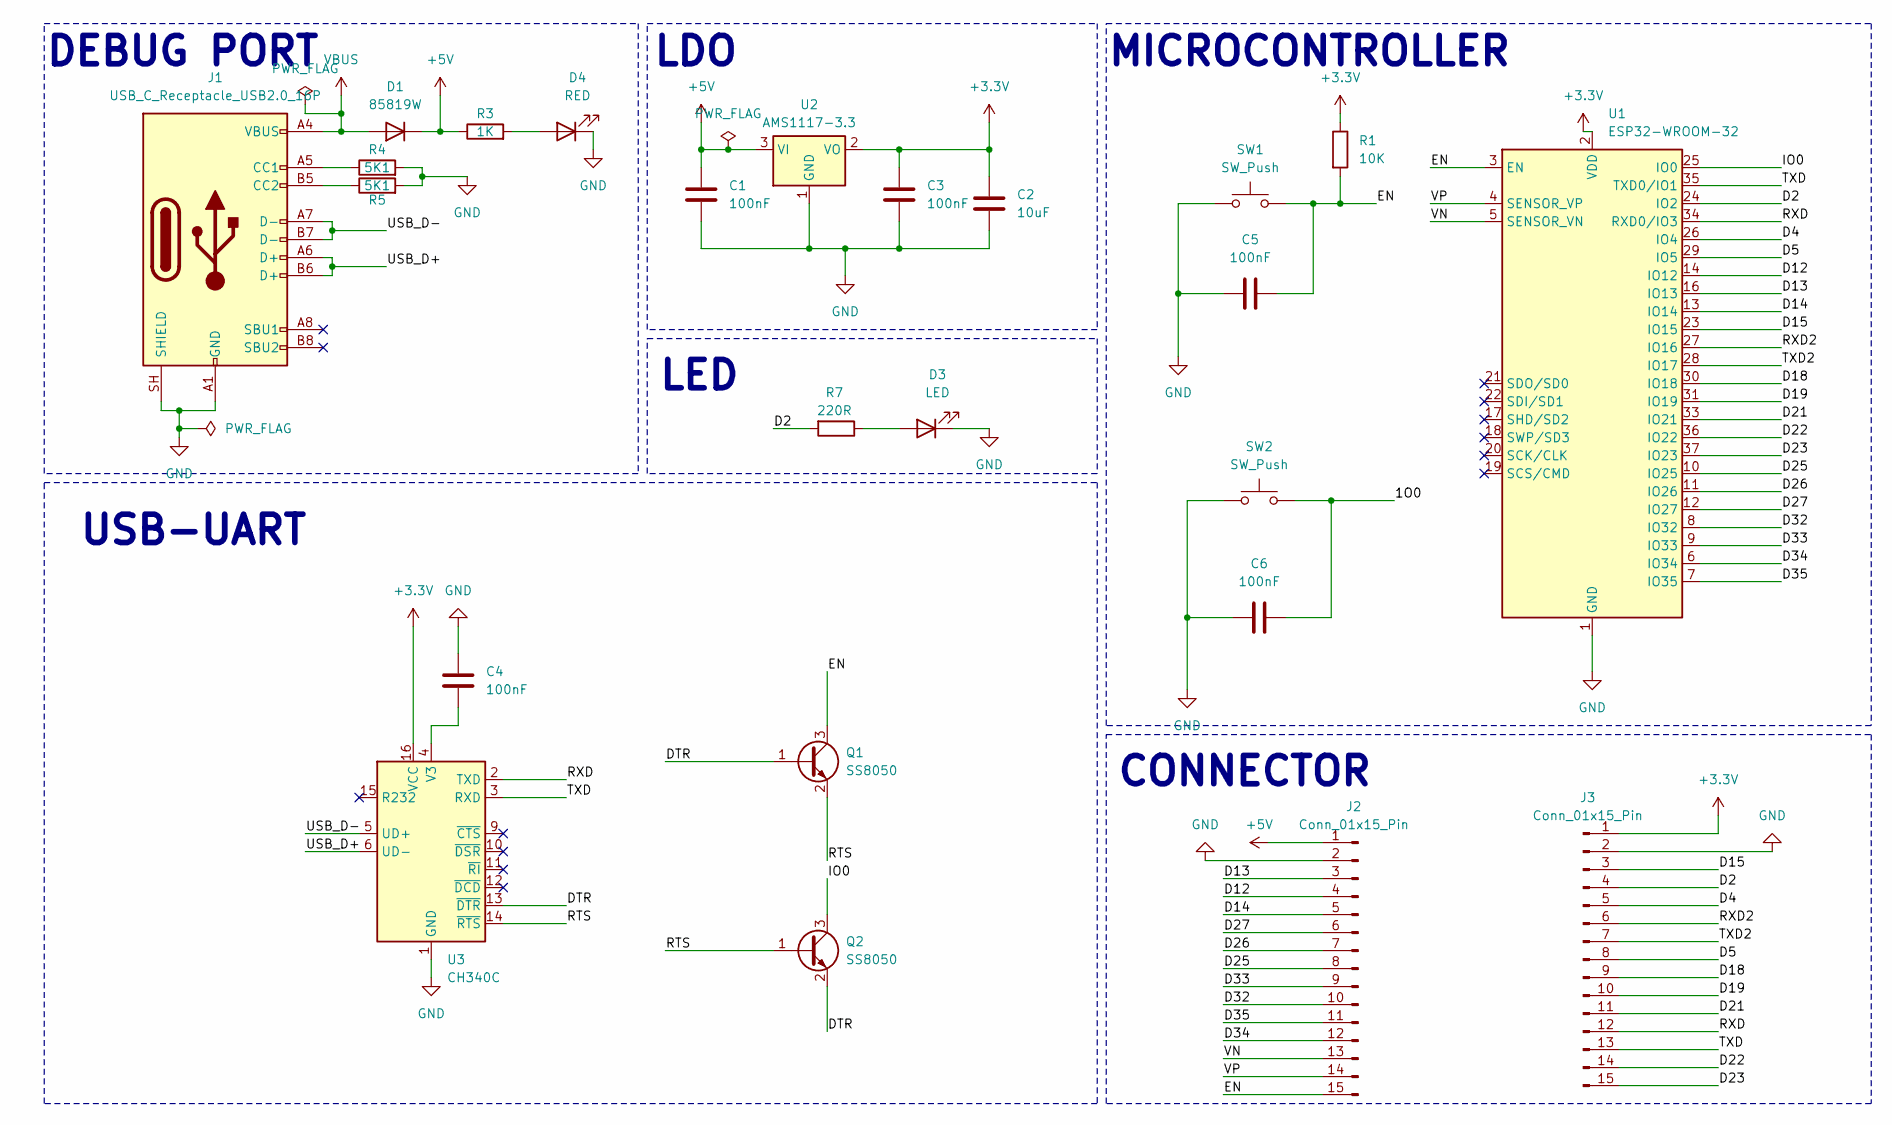
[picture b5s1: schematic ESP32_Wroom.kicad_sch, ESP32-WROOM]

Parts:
C1, C3, C4, C5, C6: 100nF; C_0603_1608Metric
C2: 10uF; C_0805_2012Metric
D1: 85819W; D_SOD-123
D3: LED; LED_0603_1608Metric
D4: RED; LED_0603_1608Metric
J1: USB_C_Receptacle_USB2.0_16P; USB_C_Receptacle_HRO_TYPE-C-31-M-12
J2, J3: Conn_01x15_Pin; PinHeader_1x15_P2.54mm_Vertical
Q1, Q2: SS8050; SOT-23
R1: 10K; R_0603_1608Metric
R3: 1K; R_0603_1608Metric
R4, R5: 5K1; R_0603_1608Metric
R7: 220R; R_0603_1608Metric
SW1, SW2: SW_Push; SW_Push_SPST_NO_Alps_SKRK
U1: ESP32-WROOM-32
U2: AMS1117-3.3; SOT-223-3_TabPin2
U3: CH340C; SOIC-16_3.9x9.9mm_P1.27mm

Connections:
+3.3V: C2.1, C3.1, J3.1, R1.1, U1.2 (VDD), U2.2 (VO), U3.16 (VCC)
+5V: C1.1, D1.1 (K), J2.1, R3.1, U2.3 (VI)
/1O0: C6.1, SW2.2
/D2: J3.4, R7.2, U1.24 (IO2)
/D4: J3.5, U1.26 (IO4)
/D5: J3.8, U1.29 (IO5)
/D12: J2.4, U1.14 (IO12)
/D13: J2.3, U1.16 (IO13)
/D14: J2.5, U1.13 (IO14)
/D15: J3.3, U1.23 (IO15)
/D18: J3.9, U1.30 (IO18)
/D19: J3.10, U1.31 (IO19)
/D21: J3.11, U1.33 (IO21)
/D22: J3.14, U1.36 (IO22)
/D23: J3.15, U1.37 (IO23)
/D25: J2.8, U1.10 (IO25)
/D26: J2.7, U1.11 (IO26)
/D27: J2.6, U1.12 (IO27)
/D32: J2.10, U1.8 (IO32)
/D33: J2.9, U1.9 (IO33)
/D34: J2.12, U1.6 (IO34)
/D35: J2.11, U1.7 (IO35)
/DTR: Q1.1 (B), Q2.2 (E), U3.13 (~DTR)
/EN: C5.1, J2.15, Q1.3 (C), R1.2, SW1.2, U1.3 (EN)
/IO0: Q2.3 (C), U1.25 (IO0)
/RTS: Q1.2 (E), Q2.1 (B), U3.14 (~RTS)
/RXD: J3.12, U1.34 (RXD0/IO3), U3.2 (TXD)
/RXD2: J3.6, U1.27 (IO16)
/TXD: J3.13, U1.35 (TXD0/IO1), U3.3 (RXD)
/TXD2: J3.7, U1.28 (IO17)
/USB_D+: J1.A6 (D+), J1.B6 (D+), U3.6 (UD-)
/USB_D-: J1.A7 (D-), J1.B7 (D-), U3.5 (UD+)
/VN: J2.13, U1.5 (SENSOR_VN)
/VP: J2.14, U1.4 (SENSOR_VP)
GND: C1.2, C2.2, C3.2, C4.1, C5.2, C6.2, D3.1 (K), D4.1 (K), J1.A1 (GND), J1.A12 (GND), J1.B1 (GND), J1.B12 (GND), J1.SH (SHIELD), J2.2, J3.2, R4.2, R5.2, SW1.1, SW2.1, U1.1 (GND), U1.15 (GND), U1.38 (GND), U1.39 (GND), U2.1 (GND), U3.1 (GND)
unnamed: D3.2 (A), R7.1
unnamed: D4.2 (A), R3.2
unnamed: J1.A5 (CC1), R4.1
unnamed: J1.B5 (CC2), R5.1
unnamed: C4.2, U3.4 (V3)
VBUS: D1.2 (A), J1.A4 (VBUS), J1.A9 (VBUS), J1.B4 (VBUS), J1.B9 (VBUS)

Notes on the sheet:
MICROCONTROLLER
LED
LDO
USB-UART
CONNECTOR
DEBUG PORT

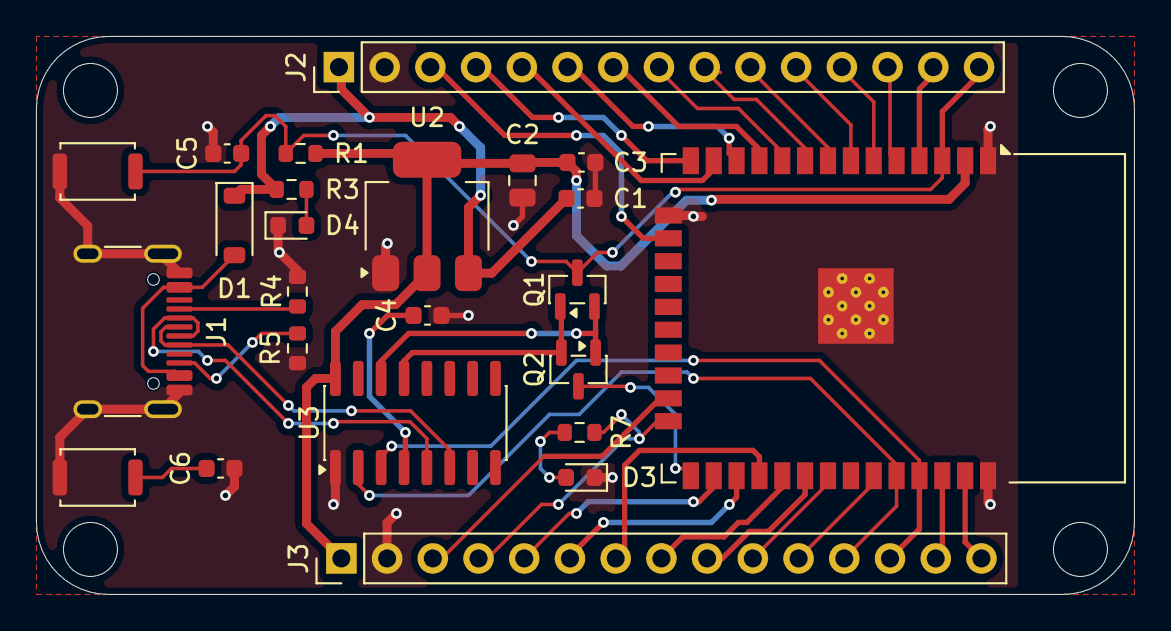
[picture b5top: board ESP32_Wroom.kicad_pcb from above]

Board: 2 copper layers, 61.0 x 31.0 mm, 24 parts (0 on the bottom side), 41 nets.
